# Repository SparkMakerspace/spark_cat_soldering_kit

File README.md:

Simple soldering kit by and for the nerds at Spark Makerspace.

Materials:
* 2 x 5mm LEDs[^1]
* 1 x BAT-HLD-001-THM
* 1 x CR2032 3V Battery Cell

[^1]: Any 5mm LEDs will do, but the ones we prefer can be found searching some combination of these words on your favorite site for sourcing cheap parts: "Slow Flashing LED Diode, Multi-Color Blinking Changing Light Emitting Diodes, 2 Pins Clear"

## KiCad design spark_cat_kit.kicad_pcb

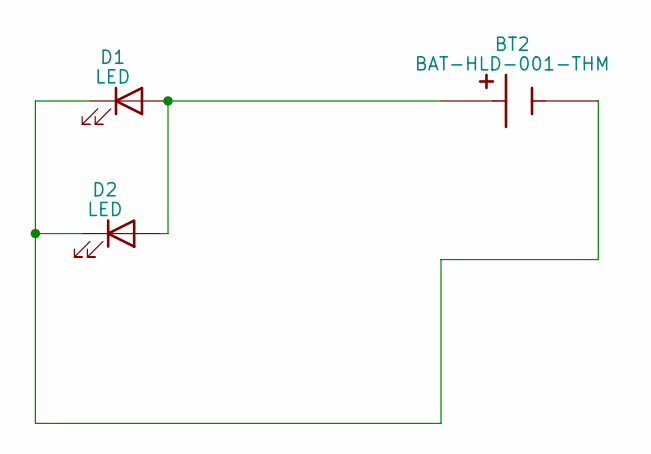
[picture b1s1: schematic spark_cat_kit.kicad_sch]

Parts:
BT2: BAT-HLD-001-THM; BAT_BAT-HLD-001-THM; PARTREV C
D1, D2: LED; LED_D5.0mm

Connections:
unnamed: BT2.P1, BT2.P2, BT2.P3, BT2.P4, D1.2 (A), D2.2 (A)
unnamed: BT2.N, D1.1 (K), D2.1 (K)

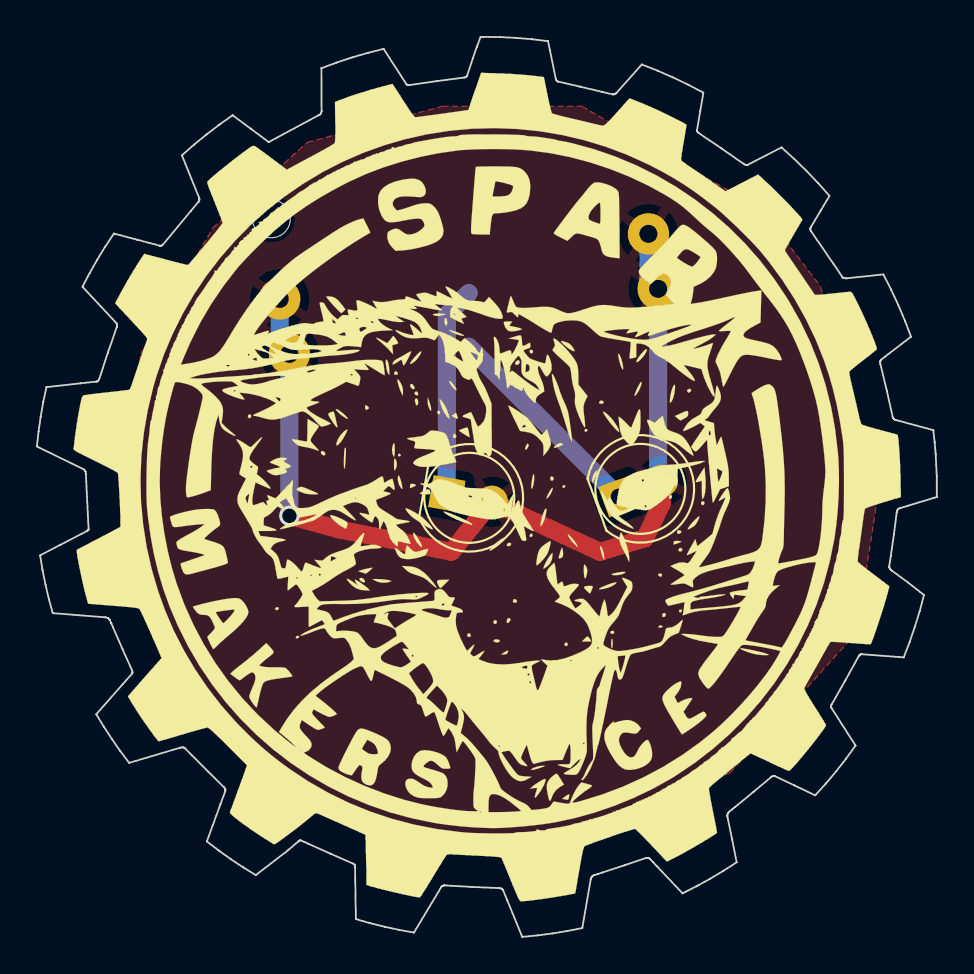
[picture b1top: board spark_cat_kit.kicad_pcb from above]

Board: 2 copper layers, 50.0 x 50.0 mm, 3 parts (1 on the bottom side), 2 nets.

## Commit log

2023-08-14 initial work
